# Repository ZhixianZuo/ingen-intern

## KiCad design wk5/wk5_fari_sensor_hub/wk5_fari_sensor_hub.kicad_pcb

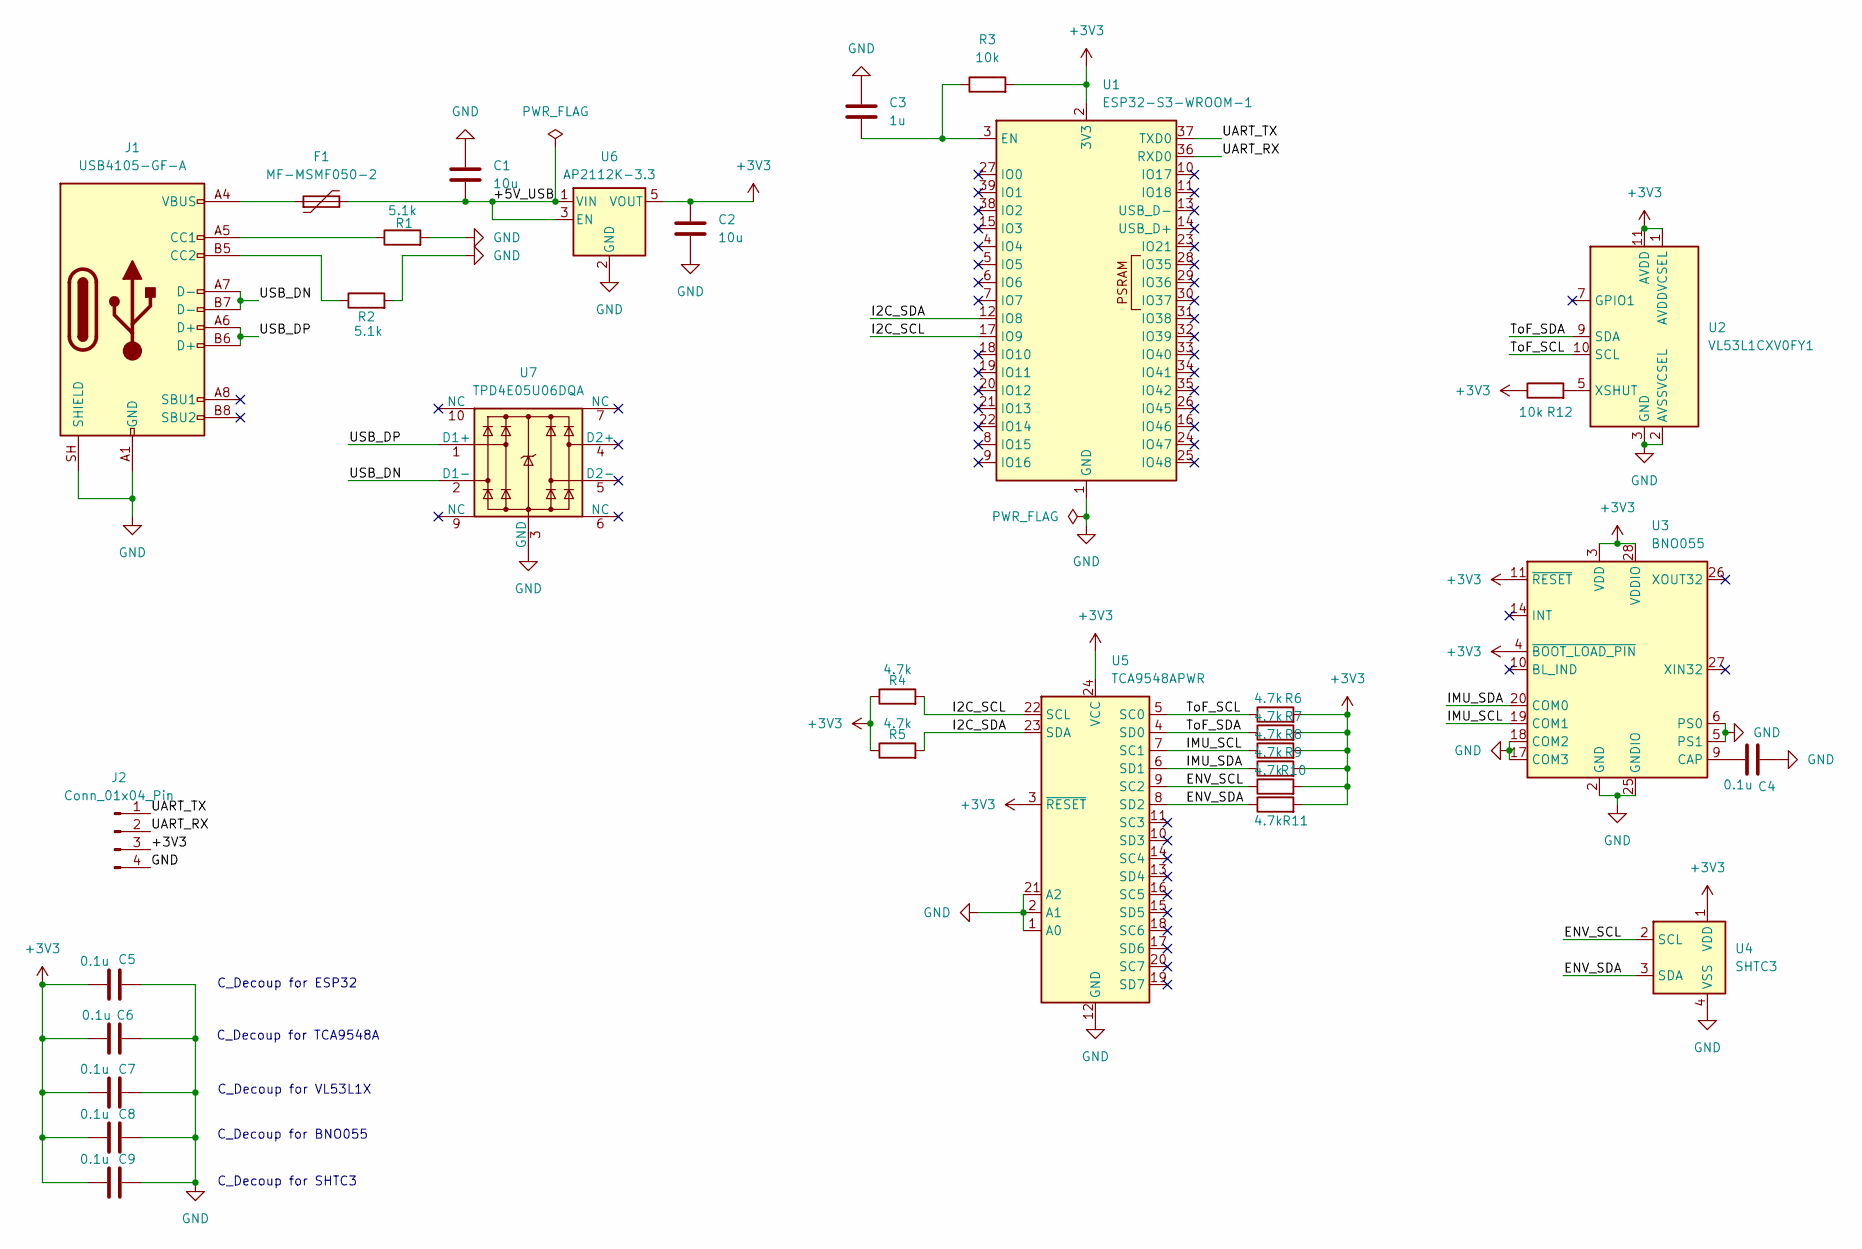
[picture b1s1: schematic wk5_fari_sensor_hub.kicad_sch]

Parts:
C1, C2: 10u; C_0603_1608Metric
C3: 1u; C_0603_1608Metric
C4, C5, C6, C7, C8, C9: 0.1u; C_0603_1608Metric
F1: MF-MSMF050-2; Fuse_0805_2012Metric
J1: USB4105-GF-A; USB_C_Receptacle_GCT_USB4105-xx-A_16P_TopMnt_Horizontal
J2: Conn_01x04_Pin; PinHeader_1x04_P2.54mm_Vertical
R1, R2: 5.1k; R_0603_1608Metric
R3, R12: 10k; R_0603_1608Metric
R4, R5, R6, R7, R8, R9, R10, R11: 4.7k; R_0603_1608Metric
U1: ESP32-S3-WROOM-1
U2: VL53L1CXV0FY1; ST_VL53L1x
U3: BNO055; LGA-28_5.2x3.8mm_P0.5mm
U4: SHTC3; Sensirion_DFN-4-1EP_2x2mm_P1mm_EP0.7x1.6mm
U5: TCA9548APWR; TSSOP-24_4.4x7.8mm_P0.65mm
U6: AP2112K-3.3; SOT-23-5
U7: TPD4E05U06DQA; USON-10_2.5x1.0mm_P0.5mm

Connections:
+3V3: C2.1, C5.1, C6.1, C7.1, C8.1, C9.1, J2.3, R3.2, R4.1, R5.1, R6.2, R7.2, R8.2, R9.2, R10.2, R11.2, R12.1, U1.2 (3V3), U2.1 (AVDDVCSEL), U2.11 (AVDD), U3.3 (VDD), U3.4 (~BOOT_LOAD_PIN), U3.11 (~RESET), U3.28 (VDDIO), U4.1 (VDD), U5.3 (~RESET), U5.24 (VCC), U6.5 (VOUT)
/+5V_USB: C1.2, F1.2, U6.1 (VIN), U6.3 (EN)
/ENV_SCL: R10.1, U4.2 (SCL), U5.9 (SC2)
/ENV_SDA: R11.1, U4.3 (SDA), U5.8 (SD2)
/I2C_SCL: R4.2, U1.17 (IO9), U5.22 (SCL)
/I2C_SDA: R5.2, U1.12 (IO8), U5.23 (SDA)
/IMU_SCL: R8.1, U3.19 (COM1), U5.7 (SC1)
/IMU_SDA: R9.1, U3.20 (COM0), U5.6 (SD1)
/ToF_SCL: R6.1, U2.10 (SCL), U5.5 (SC0)
/ToF_SDA: R7.1, U2.9 (SDA), U5.4 (SD0)
/UART_RX: J2.2, U1.36 (RXD0)
/UART_TX: J2.1, U1.37 (TXD0)
/USB_DN: J1.A7 (D-), J1.B7 (D-), U7.2 (D1-)
/USB_DP: J1.A6 (D+), J1.B6 (D+), U7.1 (D1+)
GND: C1.1, C2.2, C3.1, C4.2, C5.2, C6.2, C7.2, C8.2, C9.2, J1.A1 (GND), J1.A12 (GND), J1.B1 (GND), J1.B12 (GND), J1.SH (SHIELD), J2.4, R1.2, R2.2, U1.1 (GND), U1.40 (GND), U1.41 (GND), U2.2 (AVSSVCSEL), U2.3 (GND), U2.4 (GND), U2.6 (GND), U2.12 (GND), U3.2 (GND), U3.5 (PS1), U3.6 (PS0), U3.17 (COM3), U3.18 (COM2), U3.25 (GNDIO), U4.4 (VSS), U5.1 (A0), U5.2 (A1), U5.12 (GND), U5.21 (A2), U6.2 (GND), U7.3 (GND), U7.8 (GND)
unnamed: F1.1, J1.A4 (VBUS), J1.A9 (VBUS), J1.B4 (VBUS), J1.B9 (VBUS)
unnamed: J1.A5 (CC1), R1.1
unnamed: J1.B5 (CC2), R2.1
unnamed: C3.2, R3.1, U1.3 (EN)
unnamed: R12.2, U2.5 (XSHUT)
unnamed: C4.1, U3.9 (CAP)

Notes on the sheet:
C_Decoup for ESP32
C_Decoup for BNO055
C_Decoup for VL53L1X
C_Decoup for SHTC3
C_Decoup for TCA9548A

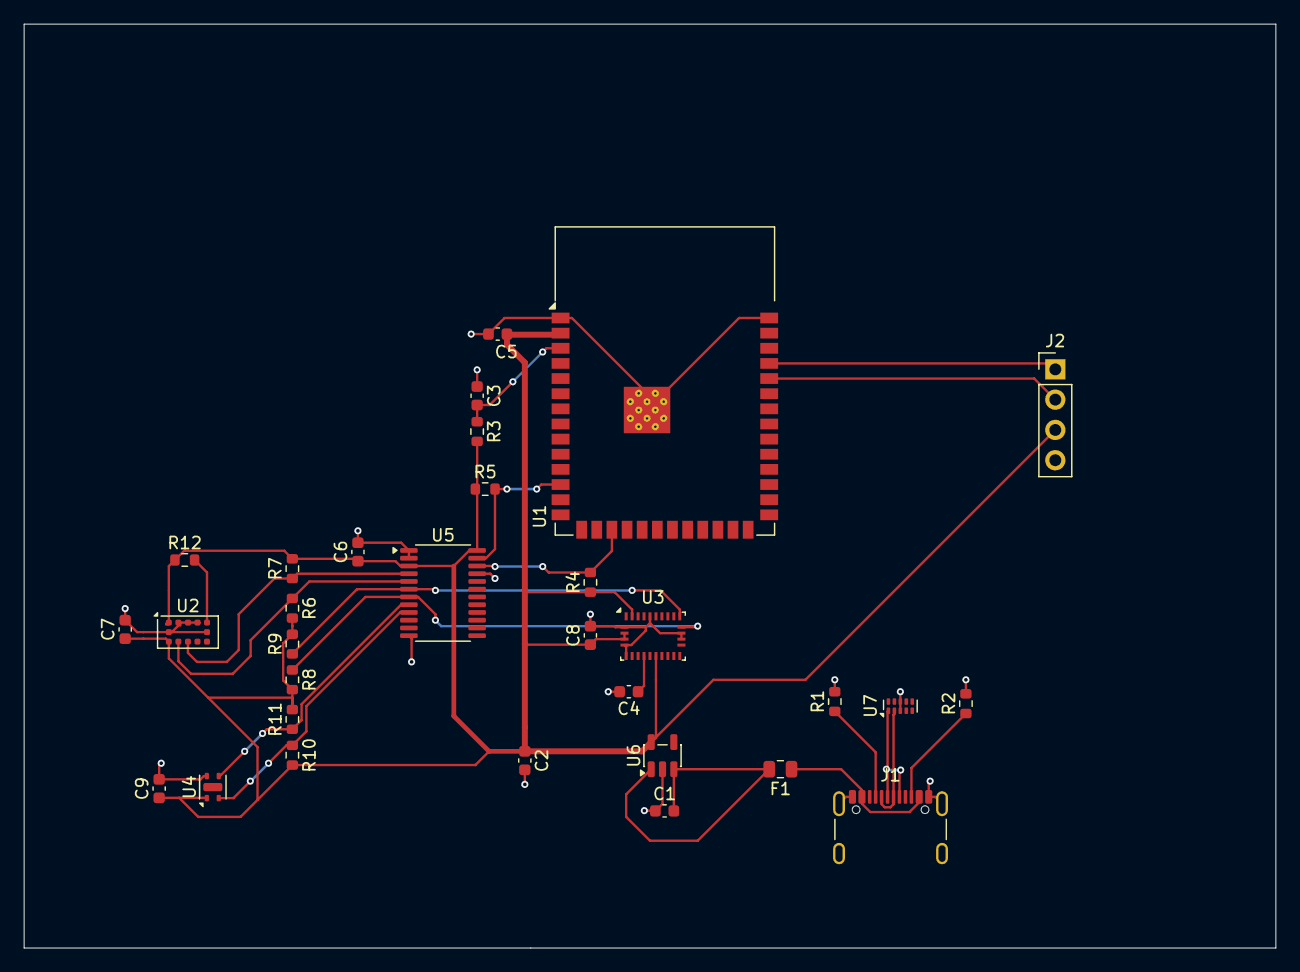
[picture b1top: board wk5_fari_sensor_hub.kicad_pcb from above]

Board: 2 copper layers, 105.0 x 77.5 mm, 31 parts (0 on the bottom side), 21 nets.

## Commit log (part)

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2026-05-25 docs: initialize 9-week workspace and complete week 1 reports
2026-05-26 docs: complete week 1 generic mobile robot block diagram
2026-05-26 docs: complete week 2 sensor selection matrix for Sentinel and Senpai
2026-06-16 docs: complete week 3 power system and BMS deliverables
2026-06-24 Create wk4
2026-06-24 week 4
2026-06-29 Create wk5
